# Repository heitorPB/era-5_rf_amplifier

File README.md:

# ERA-5+ RF Amplifier board

Evaluation board for *[EVA-5+](https://www.minicircuits.com/WebStore/dashboard.html?model=ERA-5%2B)*
amplifier from [Mini-Circuits®](http://www.minicircuits.com).

## project structure

```
.
├── 3d_models
├── datasheets
├── era-5_rf_amplifier.bak
├── era-5_rf_amplifier.kicad_pcb
├── era-5_rf_amplifier.pro
├── era-5_rf_amplifier.sch
├── images
├── lib_fp.pretty
├── lib_schm
├── pdf
└── README.md
```

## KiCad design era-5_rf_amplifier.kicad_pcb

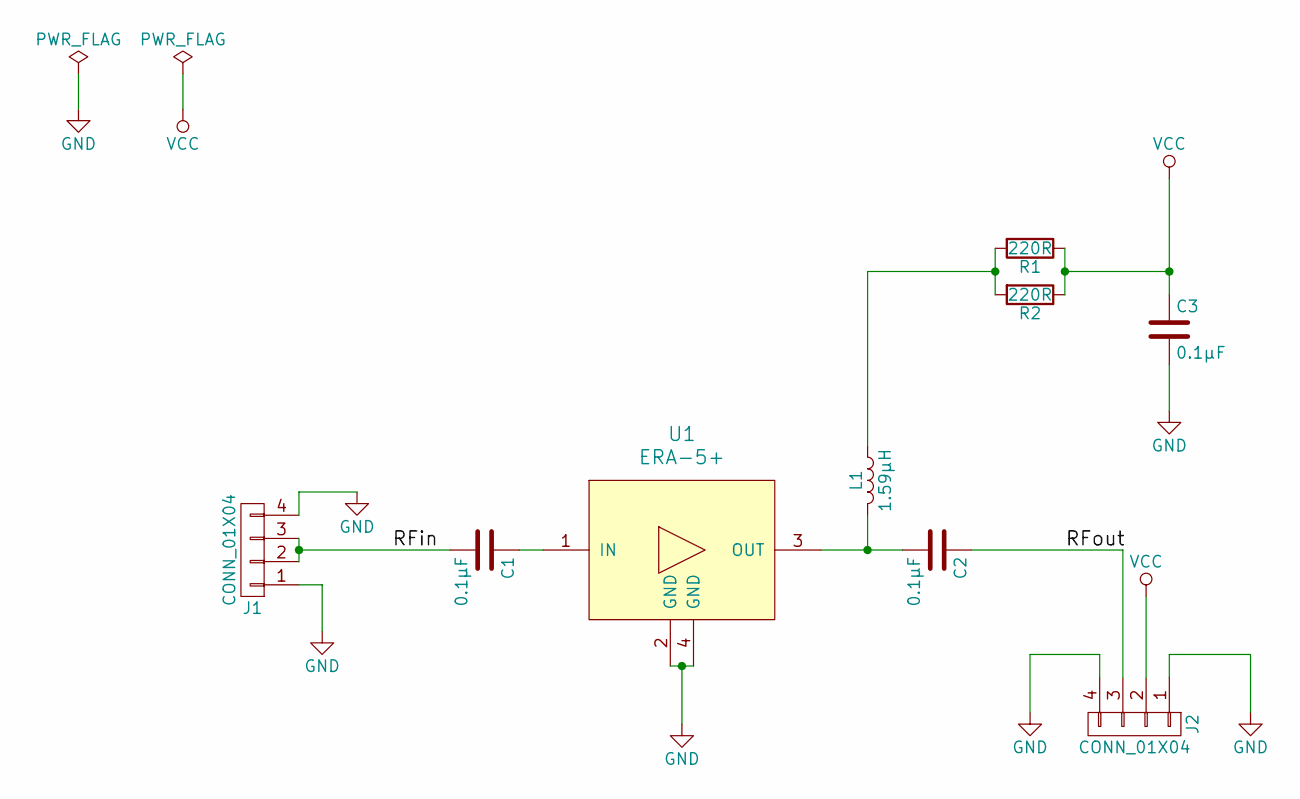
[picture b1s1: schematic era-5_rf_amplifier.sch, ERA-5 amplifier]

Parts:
C1, C2, C3: 0.1µF; C_1206_HandSoldering
J1, J2: CONN_01X04; Pin_Header_Straight_1x04_Pitch2.54mm
L1: 1.59µH; L_1812_HandSoldering
R1, R2: 220R; R_1206_HandSoldering
U1: ERA-5+; VV105

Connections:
/RFin: C1.2, J1.2, J1.3
/RFout: C2.1, J2.3
GND: C3.2, J1.1, J1.4, J2.1, J2.4, U1.2 (GND), U1.4 (GND)
unnamed: C1.1, U1.1 (IN)
unnamed: C2.2, L1.2, U1.3 (OUT)
unnamed: L1.1, R1.2, R2.2
VCC: C3.1, J2.2, R1.1, R2.1

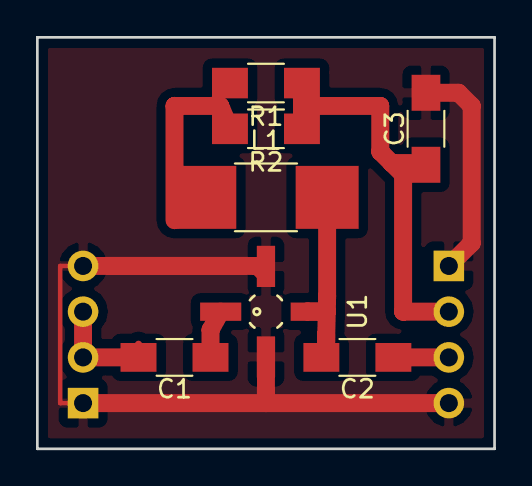
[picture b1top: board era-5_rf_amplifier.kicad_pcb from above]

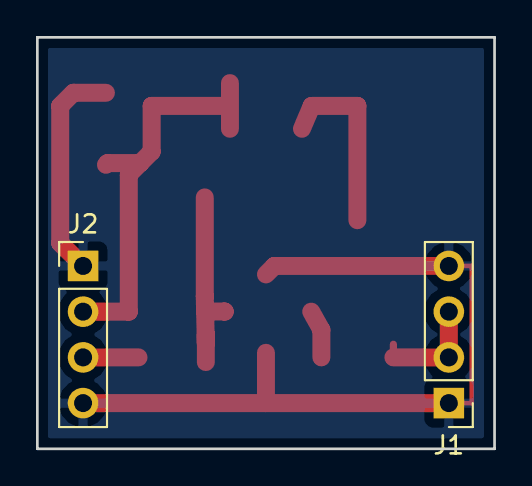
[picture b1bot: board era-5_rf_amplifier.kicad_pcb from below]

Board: 2 copper layers, 25.4 x 22.9 mm, 9 parts (2 on the bottom side), 7 nets.

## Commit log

2017-06-04 added schematic commit
2017-06-04 rearranged schematics
2017-06-04 added some footprints
2017-06-05 footprint for inductor
2017-06-12 Modified board schematic and layout
2017-06-12 Added images to README
2017-06-24 minor organization changes
2017-06-24 added local 3d shapes
